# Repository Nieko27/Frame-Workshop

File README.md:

> ⚠️ This is an unofficial 3rd-party project with no association to Valve.

# What is Frame Workshop?
Frame Workshop is intended to be an open-source bundle of different hardware peripherals built around (but not always exclusive to) the Steam Frame. The idea is to leverage the Steam Frames' modularity and general openness to create a collection of open-source hardware projects that the community can provide feedback on, expand upon, or even take and turn into something entirely new, creating a feedback loop that adds to an ever-expanding ecosystem for the Steam Frame. All source files, from schematics to STLs, will be included, allowing every aspect of each project to be modified and produced to anyone’s preferences. 

## Hardware
Below is a list of all currently in development hardware projects, including a brief overview and notes on changes made to the most recent revision.

### Agnostic Facetracker

| 🛑R&D | hw: EV2 | 
| -------- | ------- |

The Frame face tracker is pretty self-explanatory: it is a module that uses a camera for face tracking in social experiences like VRChat. There are 2 versions planned: one built with the steam frame in mind, using its expansion ports, and another that plugs into the back USB port of the frame and uses an ESP32 to run the camera.

>Headset-Agnostic Version EV2

<br>

Link to the agnostic facetracker files:
[Here](https://github.com/Nieko27/Frame-Workshop/tree/main/KICAD%20Projects/FaceTrackers/Primis_FaceTracker)

### Frame Facetracker

| 🛑R&D | hw: EV1 | 
| -------- | ------- |

Link to frame facetracker files:
[Here](https://github.com/Nieko27/Frame-Workshop/tree/main/KICAD%20Projects/FaceTrackers/Frame_FaceTracker)

### Versipellis (General Purpose Dongle)

| 🟠WIP | hw: EV2 | 
| -------- | ------- |

Versipellis is a dongle utilising an nRF52833 intended as a general-purpose dongle for communicating with any Frame-based hardware, whether it be controllers or trackers. It will be programmable by the end user for whatever they intend to use it for. There will be two versions: one utilising no parts smaller than a 0603 package, making it easy to hand-assemble, and another using much smaller parts that, while smaller, will require assembly by a service like JLCPCB.

>Hand-assemblable EV1

<br>

Link to Versipellis' files:
[Here](https://github.com/Nieko27/Frame-Workshop/tree/main/KICAD%20Projects/Dongles/Primis_Versipellis)

### VeriMini

| 🛑R&D | hw: EV1 | 
| -------- | ------- |

Link to VeriMini files:
[Here](https://github.com/Nieko27/Frame-Workshop/tree/main/KICAD%20Projects/Dongles/Primis_VeriMini)

### Locus (Tracker)

| 🟠WIP | hw: EV2 | 
| -------- | ------- |

Locus is intended to be a tracker like Vive or Tundra, but without reliance on lighthouse base stations. Since the Steam Frame isn’t limited to base station vision, trackers being used with it shouldn’t be either. Similar to Versipellis, Locus will also use an nRF52833 along with an LSM6DSV16X IMU. The idea is that it will track similarly to a slime tracker, but also use the Steam Frame’s optical tracking to address the drift problem of EMF trackers. 

Link to Locus' files:
[Here](https://github.com/Nieko27/FrameWork/tree/main/KICAD%20Projects/Primis_Locus)

## Project Status Indicator

| 🔵STATUS | hw: EV1 | fw: v0.0.0 | sw: v0.0.0 |
| -------- | ------- | ---------- | ---------- |

The above status indicator is listed for each Frame Workshop accessory. It shows overall progress as well as the latest upstreamed hardware, firmware, and/or software versions. Here's what each status means:

**🔴R&D**: This accessory is experimental. The latest hardware revision is either untested, incomplete, or broken. Capabilities are unproven. Form factor and design requirements may change entirely. Intended for use by hardware contributors.

**🟠WIP**: The current hardware revision has been tested and is fully capable of meeting established design requirements. Firmware and/or software are in active development. Future hardware revisions may still follow if oversights or improvements are discovered. Intended for use by software contributors.

**🟡PRE**: This accessory has reached a pre-release stage. Hardware is finalized. Firmware and software meets functional requirements but may still be buggy or unintuitive. Documentation is not yet up to release standards. Considered usable for tinkerers and early adopters.

**🟢REL**: This accessory is considered released and fully functional both in software and hardware. Documentation is available to assist with ordering components, assembly, and usage. Software and firmware QOL updates may still follow but will be distributed through user friendly means.

### Future Projects
* USB Hub
* Index speaker mod kit

## Accessories and CAD
While 3D models for each electronics project are in the 3D models folder, I also plan to make several other CAD files available for accessories that don't require electronics. Things like lens caps, headset stands, battery or IO expansion holders, etc.
<br>
https://github.com/Nieko27/Frame-Workshop/tree/main/3D%20Models/Accessories

## Project Goals

* Keep costs to the users as low as possible. You've already spent over a $1000 on the headset itself, so it would be nice not to have to spend another $1000 customizing it to your liking. How this would be achieved is by everything being open and nothing being sold, for example I’m working on a face tracker that takes advantage of the PCIe port on the Frame, the idea is when its done instead of me having to handle production, shipping and all the joys of selling a project I give the source files out with a tutorial on how to order it yourself from a company like JLCPCB. Now, obviously, this still won't be free to the end user, but it will be much cheaper than if I were to sell it. For example, I have made the first prototype of the face-tracker, and in small quantities (5 to be exact), it cost me $25 per board. Compare that to something like the old Vive face trackers, which I think were closer to $100, and you save a nice bit of money. 

* Give the end user total control over the hardware. Don't like how I've done something? Fire up Blender or KiCad and change it yourself to fit whatever need you have in mind. I know not everyone will be able to do this, as it requires familiarity with the software, but it gives people the ability to do so. Obviously, with this in mind, I want to make the experience for everyone as smooth as possible out of the box, so I will be listening to feedback as much as possible to achieve that. 

* Create a feedback loop. I have all this under a CERN-OHL-S-2.0 license, which (as far as I understand) means you can do anything you want with anything in the repo, including selling it for profit, but you must open-source anything you do under the same license. This way it keeps everything open to the community, and every addition helps grow the ecosystem around the Steam Frame. 

## Note
A forewarning, I am very new to electronics design in general. I apologize in advance for any really baffling design decisions. I hope to learn from these projects and will keep them updated as I learn more. Thank you for your patience.

## Ideas
A few ideas for possible mods for the Frame have already been thrown around. If you have an idea for a mod, whether it's a full module or as simple as a 3D-printable counterweight, feel free to open a pull request under the enhancement tag. You may also feel free to email me at nieko972@gmail.com.

### Find me on
* Twitter; https://x.com/Merlinr271
* Bluesky; https://bsky.app/profile/merlin271.bsky.social

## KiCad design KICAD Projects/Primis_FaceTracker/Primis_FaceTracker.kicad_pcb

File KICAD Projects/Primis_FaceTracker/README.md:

### Status

| 🛑R&D | hw: EV2 | 
| -------- | ------- |

> This accessory is experimental. The latest hardware revision is either untested, incomplete, or broken. Capabilities are unproven. Form factor and design requirements may change entirely. Intended for use by hardware contributors.

### TODO
* Copper pads under power supply
* Clean up and condense
* ESD Protection
# Face Tracker (Headset-Agnostic Version)
Headset-agnostic face tracker. Can be used with Frame by using the USB-C port on the battery.
## Current Isseus
Q1 is setup improperly, removing it and R10 as well as bridging the now empty pads solves the issue. Will fix in EV3 along with some changes to layout and LEDs.

### Schematics

### PCB

### EV2

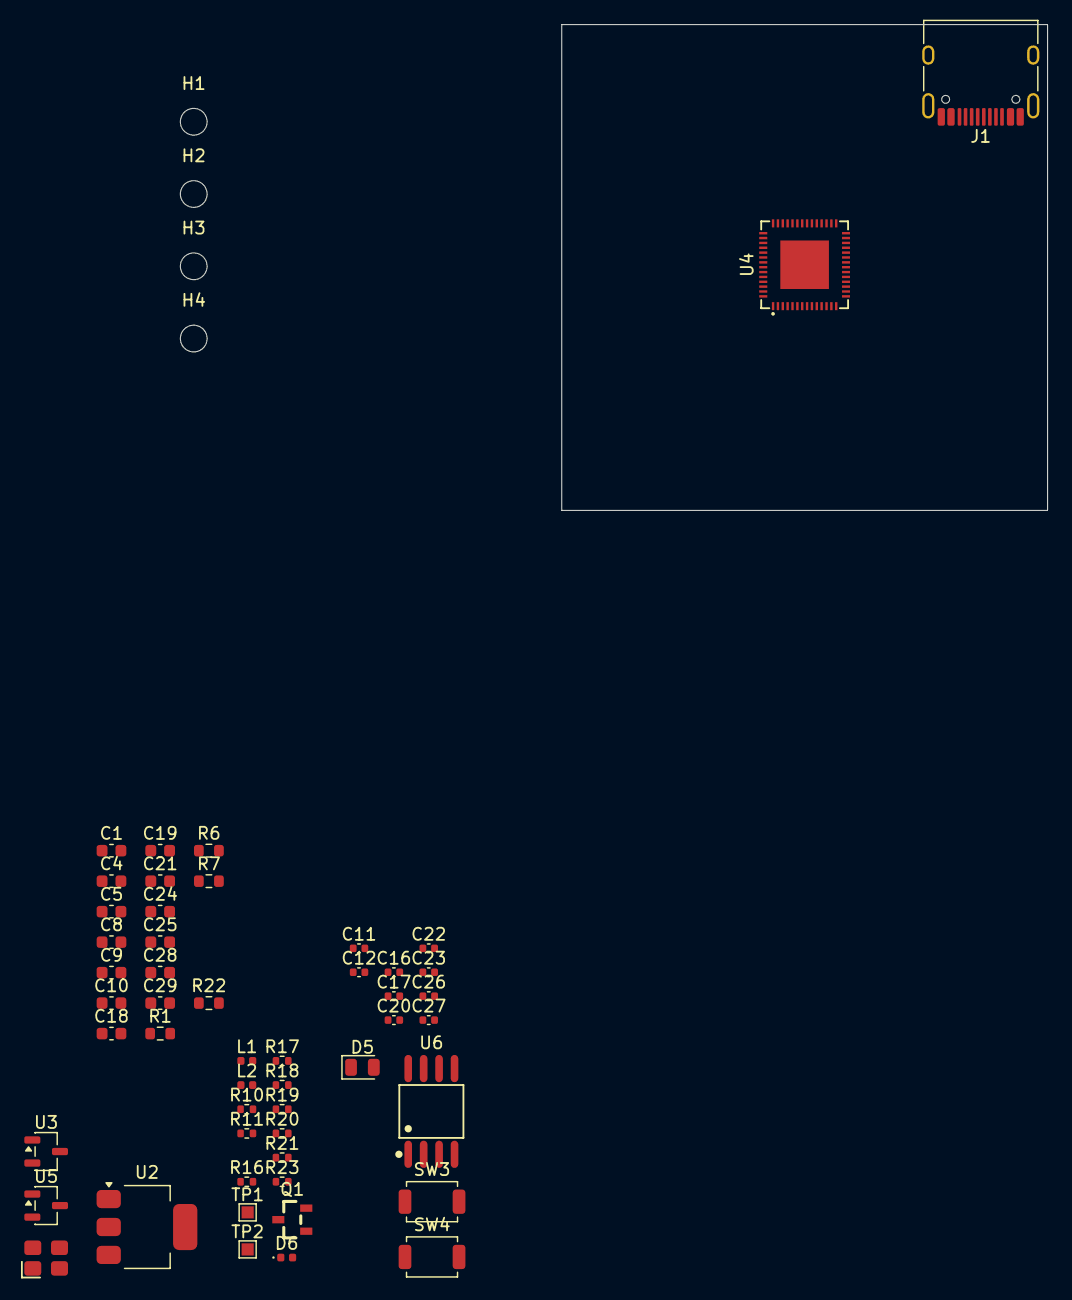
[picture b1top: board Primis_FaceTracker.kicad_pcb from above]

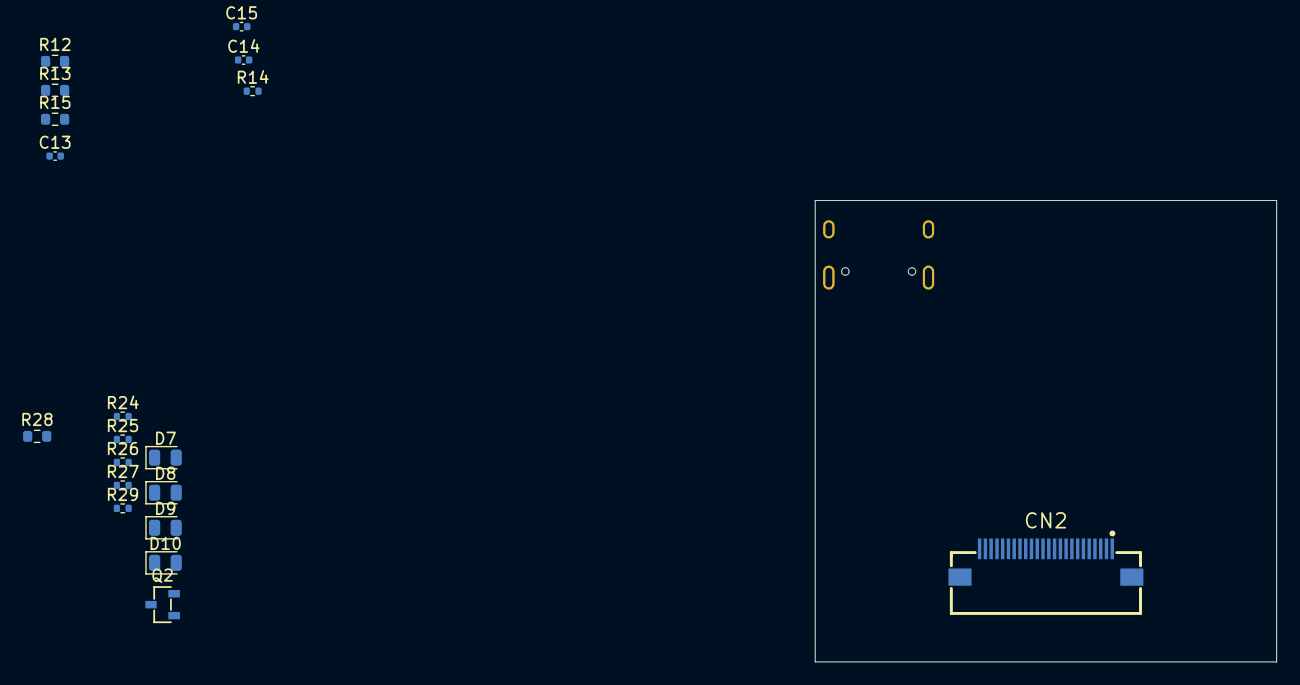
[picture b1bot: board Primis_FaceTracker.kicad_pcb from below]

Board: 2 copper layers, 74 parts (19 on the bottom side), 58 nets, no tracks yet.

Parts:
C1, C4, C8, C9, C10, C19, C24, C28: 10uf; C_0603_1608Metric
C5: 100uf; C_0603_1608Metric
C11, C12, C13, C14, C16, C17, C20, C22, C23: 0.1uf; C_0402_1005Metric
C15: 15pF; C_0402_1005Metric
C18, C21, C25, C29: 1uf; C_0603_1608Metric
C26, C27: 22pf; C_0402_1005Metric
CN2: KH-FG0.5-H2.0-24PIN; FPC-SMD_KH-FG0.5-H2.0-24PIN
D5, D7, D8, D9, D10: LED; LED_0805_2012Metric
D6: D_TVS; D_0402_1005Metric
H1, H2, H3, H4: MountingHole; MountingHole_2.2mm_M2
J1: USB_C_Receptacle_USB2.0_16P; USB_C_Receptacle_HRO_TYPE-C-31-M-12
L1: 2.0nh; L_0402_1005Metric
L2: 24nh; L_0402_1005Metric
Q1: AO3401A
Q2: AO3400A
R1, R22: 10k; R_0603_1608Metric
R6, R7: 5.1k; R_0603_1608Metric
R10, R11, R14: 1k; R_0402_1005Metric
R12, R13, R15: 4.7k; R_0603_1608Metric
R16, R17, R18, R19, R20: 0r; R_0402_1005Metric
R21: 499r; R_0402_1005Metric
R23, R24, R25, R26, R27, R29: 100r; R_0402_1005Metric
R28: 100K; R_0603_1608Metric
SW3, SW4: SW_SPST; SW_SPST_TS-1088-xR020
TP1, TP2: TestPoint; TestPoint_Pad_1.0x1.0mm
U2: AMS1117-3.3; SOT-223-3_TabPin2
U3: XC6206P122MR; SOT-23-3
U4: ESP32-S3_R8
U5: XC6206P282MR; SOT-23-3
U6: W25Q128JVSIQTR
X1: 40MHz, 15pF; OSC-SMD_4P-L3.2-W2.5-BL_SIT8008BI

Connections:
+3V3: C1.1, C5.1, C14.1, C17.1, C18.1, C19.1, C20.1, C23.1, C24.1, C25.1, C28.1, CN2.11, D6.1 (A1), L1.1, Q1.2 (S), R1.2, R11.2, R12.1, R13.1, R15.1, R22.2, R24.2, R25.2, R26.2, R29.2, U2.2 (VO), U4.20 (VDD3P3_RTC), U4.46 (VDD3P3_CPU), U4.55 (VDDA), U4.56 (VDDA)
+5V: C4.1, J1.A4 (VBUS), J1.A9 (VBUS), J1.B4 (VBUS), J1.B9 (VBUS), U2.3 (VI)
BOOT: R23.1, U4.5 (GPIO0)
CAM_1.2V: C10.1, C12.1, CN2.10, U3.2 (VO)
CAM_2.8V: C9.1, C11.1, CN2.4, U5.2 (VO)
CAM_D0: CN2.19, U4.18 (GPIO13)
CAM_D1: CN2.21, U4.23 (GPIO17)
CAM_D2: CN2.22, U4.24 (GPIO18)
CAM_D3: CN2.20, U4.19 (GPIO14)
CAM_D4: CN2.18, U4.17 (GPIO12)
CAM_D5: CN2.16, U4.15 (GPIO10)
CAM_D6: CN2.14, U4.14 (GPIO9)
CAM_D7: CN2.12, U4.12 (GPIO7)
CAM_HSYNC: CN2.9, U4.7 (GPIO2)
CAM_MCLK: CN2.13, U4.13 (GPIO8)
CAM_PCLK: C15.1, CN2.17, U4.16 (GPIO11)
CAM_PWR: R10.1, U4.27 (GPIO21)
CAM_RST: C13.1, CN2.6, R15.2, U4.11 (GPIO6)
CAM_SCK: CN2.5, R12.2, U4.10 (GPIO5)
CAM_SDA: CN2.3, R13.2, U4.9 (GPIO4)
CAM_VSYNC: CN2.7, U4.6 (GPIO1)
D+: J1.A6 (D+), J1.B6 (D+), U4.26 (GPIO20)
D-: J1.A7 (D-), J1.B7 (D-), U4.25 (GPIO19)
EN: C29.1, R22.1, SW3.1 (A), U4.4 (CHIP_PU)
GND: C1.2, C4.2, C5.2, C8.2, C9.2, C10.2, C11.2, C12.2, C13.2, C14.2, C15.2, C16.2, C17.2, C18.2, C19.2, C20.2, C21.2, C22.2, C23.2, C24.2, C25.2, C26.2, C27.2, C28.2, C29.2, CN2.2, CN2.15, CN2.25, CN2.26, D5.1 (K), D6.2 (A2), J1.A1 (GND), J1.A12 (GND), J1.B1 (GND), J1.B12 (GND), Q2.2 (S), R6.1, R7.1, R14.2, R28.1, SW3.2 (B), SW4.2 (B), U2.1 (GND), U3.1 (GND), U4.57 (GND), U5.1 (GND), U6.4 (GND), X1.2 (GND), X1.4 (GND)
LED_PWM: R27.1, U4.43 (GPIO38)
unnamed: C16.1, L1.2, U4.2 (VDD3P3), U4.3 (VDD3P3)
unnamed: C27.1, L2.2, X1.1 (OSC)
unnamed: CN2.8, R14.1
unnamed: D5.2 (A), R11.1
unnamed: D7.2 (A), R24.1
unnamed: D8.2 (A), R25.1
unnamed: D9.2 (A), R26.1
unnamed: D10.2 (A), R29.1
unnamed: D7.1 (K), D8.1 (K), D9.1 (K), D10.1 (K), Q2.3 (D)
unnamed: J1.A5 (CC1), R6.2
unnamed: J1.B5 (CC2), R7.2
unnamed: C8.1, Q1.3 (D), U3.3 (VI), U5.3 (VI)
unnamed: Q1.1 (G), R1.1, R10.2
unnamed: Q2.1 (G), R27.2, R28.2
unnamed: R21.2, TP1.1 (1_1)
unnamed: R23.2, SW4.1 (A)
unnamed: R18.1, U4.33 (SPICLK)
unnamed: R20.1, U4.35 (SPID)
unnamed: R16.1, U4.30 (SPIHD)
unnamed: R19.1, U4.34 (SPIQ)
unnamed: R17.1, U4.31 (SPIWP)
unnamed: TP2.1 (1_1), U4.50 (U0RXD)
unnamed: R21.1, U4.49 (U0TXD)
unnamed: C26.1, U4.53 (XTAL_N), X1.3 (OSC)
unnamed: L2.1, U4.54 (XTAL_P)
SPICLK: R18.2, U6.6 (CLK)
SPICS0: U4.32 (SPICS0), U6.1 (CS#)
SPID: R20.2, U6.5 (DI)
SPIHD: R16.2, U6.7 (IO3)
SPIQ: R19.2, U6.2 (DO)
SPIWP: R17.2, U6.3 (IO2)
VDD_SPI: C21.1, C22.1, U4.29 (VDD_SPI), U6.8 (VCC)

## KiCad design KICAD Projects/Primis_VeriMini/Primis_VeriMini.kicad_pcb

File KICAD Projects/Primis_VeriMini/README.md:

### Status

| 🛑R&D | hw: EV1 | 
| -------- | ------- |

> This accessory is experimental. The latest hardware revision is either untested, incomplete, or broken. Capabilities are unproven. Form factor and design requirements may change entirely. Intended for use by hardware contributors.

# VERI-MINI
The general purpose dongle for the Steam Frame but smaller.

### Schematics

### PCB

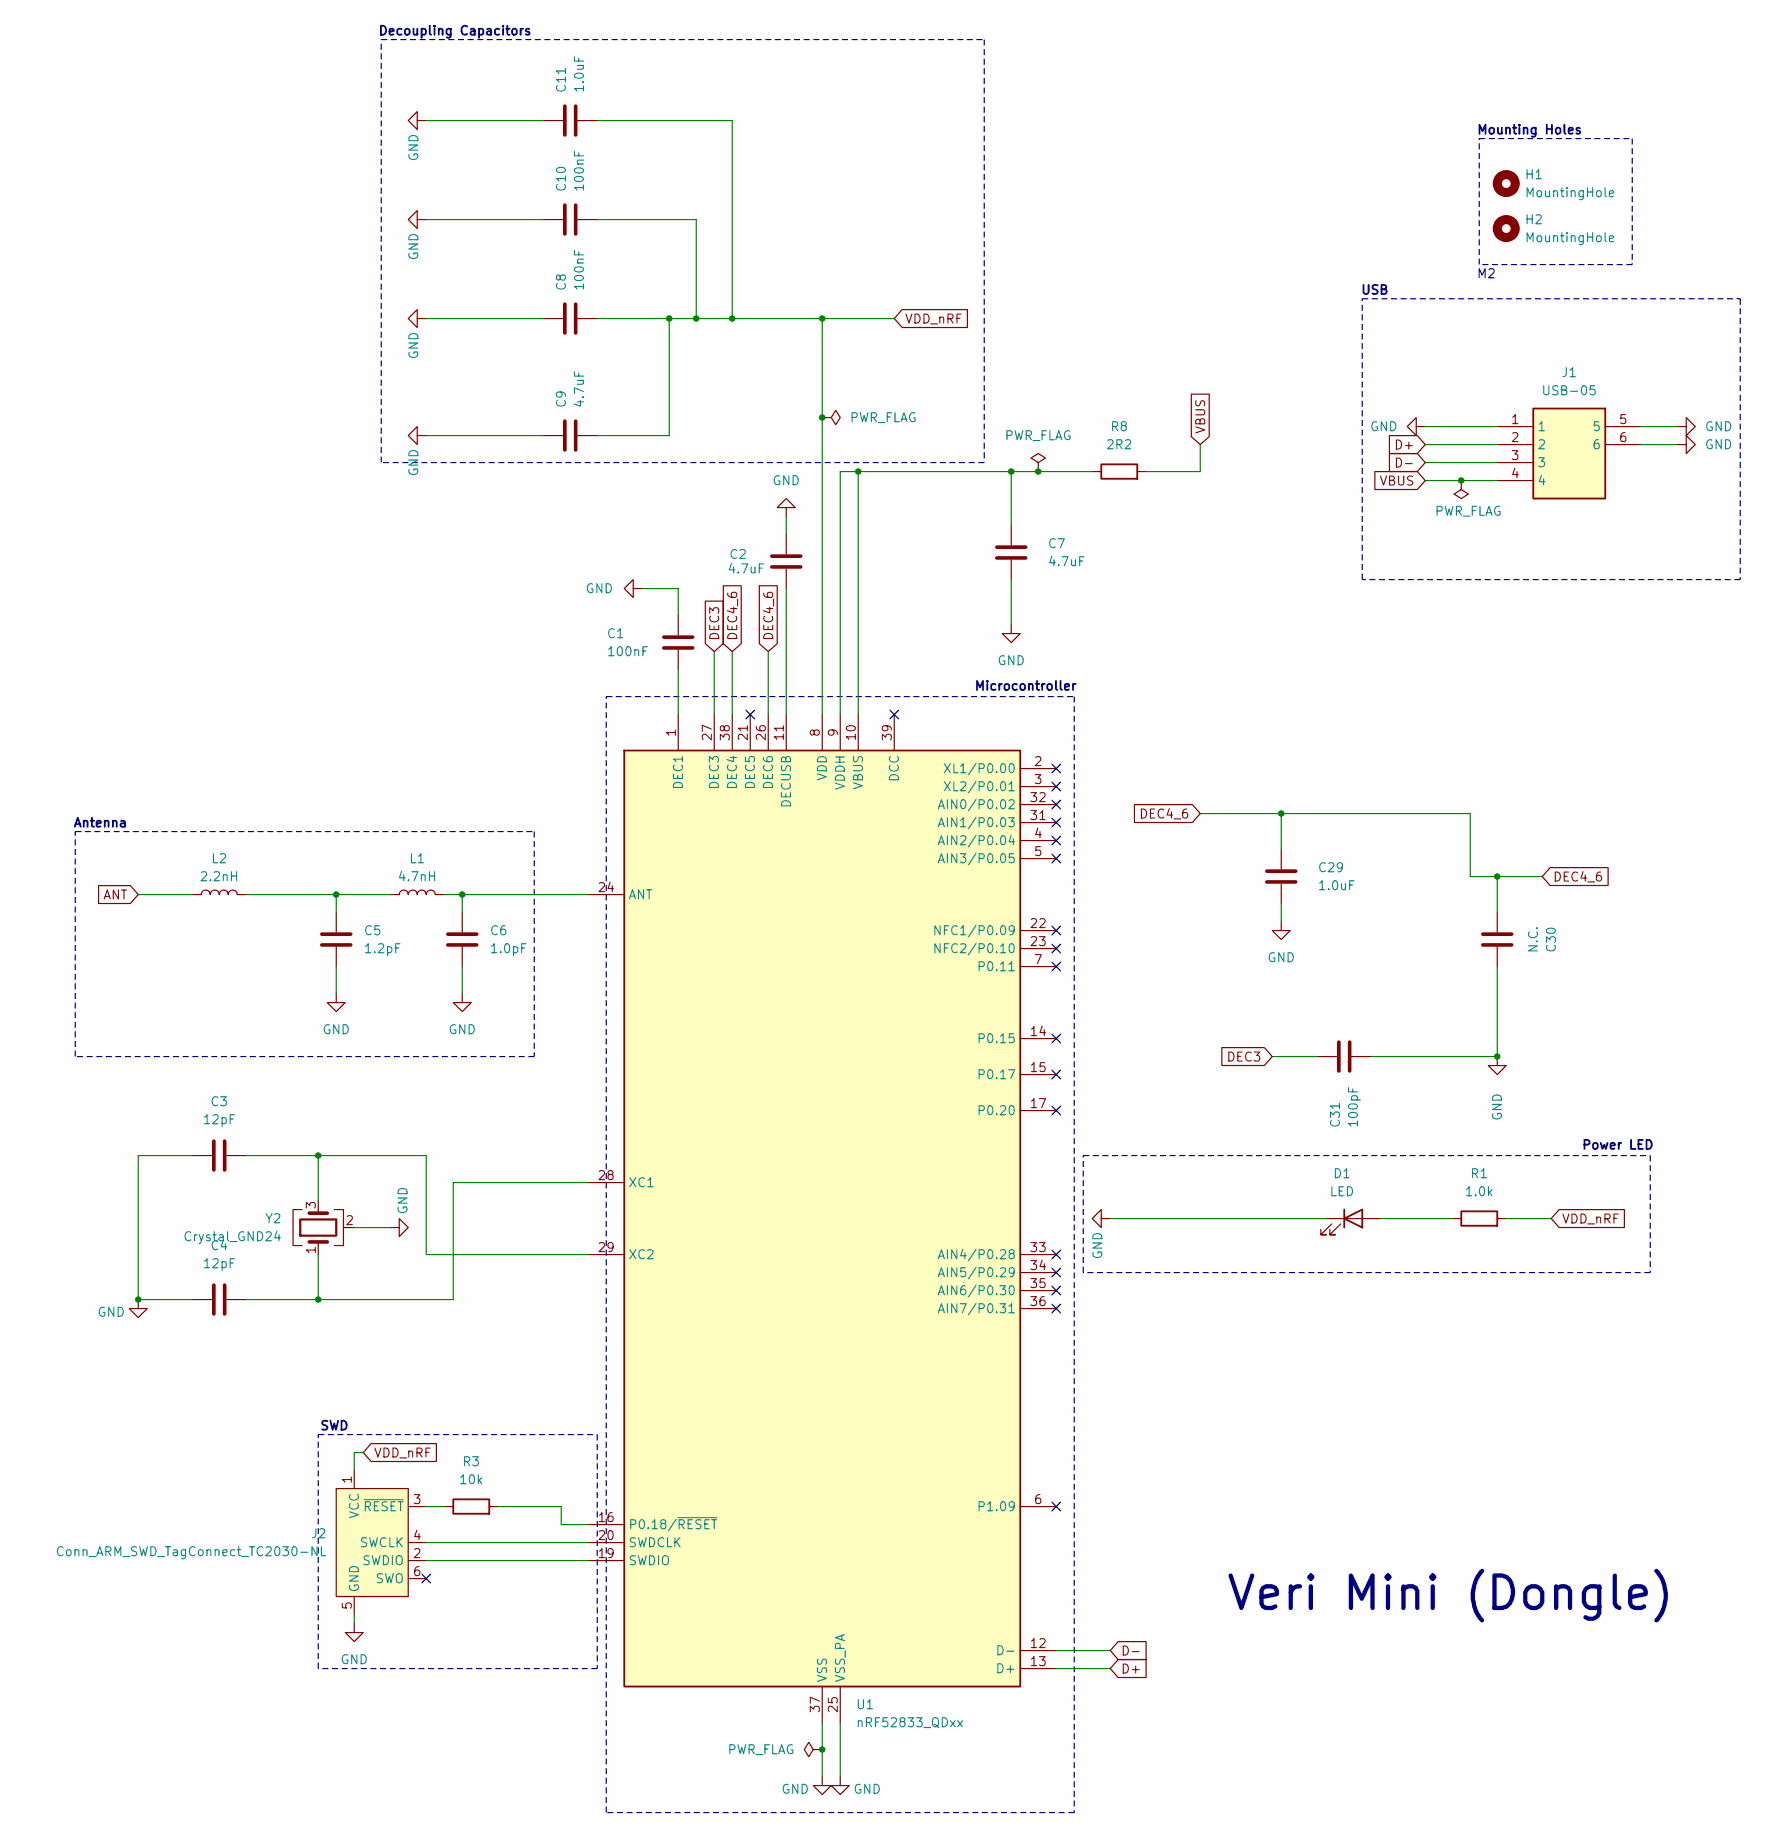
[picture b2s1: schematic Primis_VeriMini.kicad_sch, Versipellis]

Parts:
C1, C8, C10: 100nF; C_0402_1005Metric
C2, C7, C9: 4.7uF; C_0603_1608Metric
C3, C4: 12pF; C_0402_1005Metric
C5: 1.2pF; C_0402_1005Metric
C6: 1.0pF; C_0402_1005Metric
C11, C29: 1.0uF; C_0402_1005Metric
C30: N.C.; C_0402_1005Metric
C31: 100pF; C_0402_1005Metric
D1: LED; LED_0603_1608Metric
H1, H2: MountingHole; MountingHole_2.2mm_M2
J1: USB-05; USB05; Manufacturer_Part_Number USB-05
J2: Conn_ARM_SWD_TagConnect_TC2030-NL; Tag-Connect_TC2030-IDC-NL_2x03_P1.27mm_Vertical
L1: 4.7nH; L_0402_1005Metric
L2: 2.2nH; L_0402_1005Metric
R1: 1.0k; R_0402_1005Metric
R3: 10k; R_0603_1608Metric
R8: 2R2; R_0603_1608Metric
U1: nRF52833_QDxx; QFN-40-1EP_5x5mm_P0.4mm_EP3.6x3.6mm
Y2: Crystal_GND24; Crystal_SMD_Abracon_ABM8G-4Pin_3.2x2.5mm

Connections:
ANT: L2.1
D+: J1.2, U1.13 (D+)
D-: J1.3, U1.12 (D-)
DEC3: C31.1, U1.27 (DEC3)
DEC4_6: C29.1, C30.2, U1.26 (DEC6), U1.38 (DEC4)
GND: C1.1, C2.2, C3.1, C4.1, C5.1, C6.1, C7.2, C8.1, C9.2, C10.1, C11.2, C29.2, C30.1, C31.2, D1.1 (K), J1.1, J1.5, J1.6, J2.5 (GND), U1.25 (VSS_PA), U1.37 (VSS), U1.41 (VSS), Y2.2 (G), Y2.4 (G)
unnamed: C5.2, L1.1, L2.2
unnamed: D1.2 (A), R1.1
unnamed: J2.4 (SWCLK), U1.20 (SWDCLK)
unnamed: J2.2 (SWDIO), U1.19 (SWDIO)
unnamed: J2.3 (~RESET), R3.1
unnamed: C6.2, L1.2, U1.24 (ANT)
unnamed: C1.2, U1.1 (DEC1)
unnamed: C2.1, U1.11 (DECUSB)
unnamed: R3.2, U1.16 (P0.18/~RESET)
unnamed: C7.1, R8.1, U1.9 (VDDH), U1.10 (VBUS)
unnamed: C4.2, U1.28 (XC1), Y2.1
unnamed: C3.2, U1.29 (XC2), Y2.3
VBUS: J1.4, R8.2
VDD_nRF: C8.2, C9.1, C10.2, C11.1, J2.1 (VCC), R1.2, U1.8 (VDD), U1.18 (VDD), U1.30 (VDD), U1.40 (VDD)

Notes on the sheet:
Mounting Holes
Decoupling Capacitors
Microcontroller
Veri Mini (Dongle)
SWD
Antenna
Power LED
USB

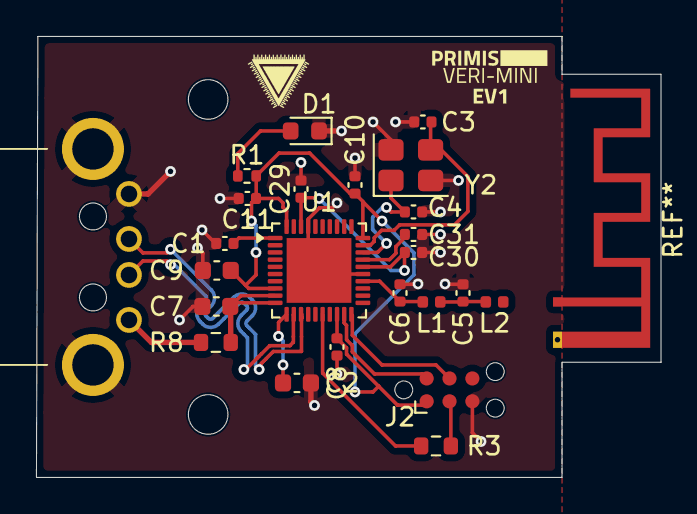
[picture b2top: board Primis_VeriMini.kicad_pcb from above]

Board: 2 copper layers, 34.7 x 24.5 mm, 26 parts (0 on the bottom side), 19 nets.

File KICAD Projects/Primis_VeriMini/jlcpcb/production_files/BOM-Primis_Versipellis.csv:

Comment,Designator,Footprint,LCSC,Quantity
1.2pF,C5,C_0603_1608Metric,,1
2R2,R8,R_0805_2012Metric,,1
1.0pF,C6,C_0603_1608Metric,,1
12pF,C4,C_0603_1608Metric,,1
4.7uF,C2,C_0603_1608Metric,,1
USB-05,J1,USB05,,1
WS2812B-2020,D3,LED_WS2812B-2020_PLCC4_2.0x2.0mm,,1
4.7uF,C9,C_0603_1608Metric,,1
nRF52833_QDxx,U1,QFN-40-1EP_5x5mm_P0.4mm_EP3.6x3.6mm,,1
100nF,C8,C_0603_1608Metric,,1
12pF,C3,C_0603_1608Metric,,1
100pF,C31,C_0603_1608Metric,,1
1.0k,R1,R_0603_1608Metric,,1
4.7uF,C7,C_0603_1608Metric,,1
LED,D1,LED_0603_1608Metric,,1
N.C.,C30,C_0603_1608Metric,,1
1.0uF,C29,C_0603_1608Metric,,1
1.0uF,C11,C_0603_1608Metric,,1
Crystal_GND24,Y2,Crystal_SMD_Abracon_ABM8G-4Pin_3.2x2.5mm,,1
100nF,C10,C_0603_1608Metric,,1
2.2nH,L2,L_0603_1608Metric,,1
10k,R3,R_0603_1608Metric,,1
4.7nH,L1,L_0603_1608Metric,,1
100nF,C1,C_0603_1608Metric,,1
100nF,C12,C_0603_1608Metric,,1

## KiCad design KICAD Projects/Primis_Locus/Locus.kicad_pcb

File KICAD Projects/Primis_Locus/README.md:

### Status

| 🟠WIP | hw: EV2 | 
| -------- | ------- |

> The current hardware revision has been tested and is fully capable of meeting established design requirements. Firmware and/or software are in active development. Future hardware revisions may still follow if oversights or improvements are discovered. Intended for use by software contributors.

### Schematics

### PCB

### EV1

### EV2

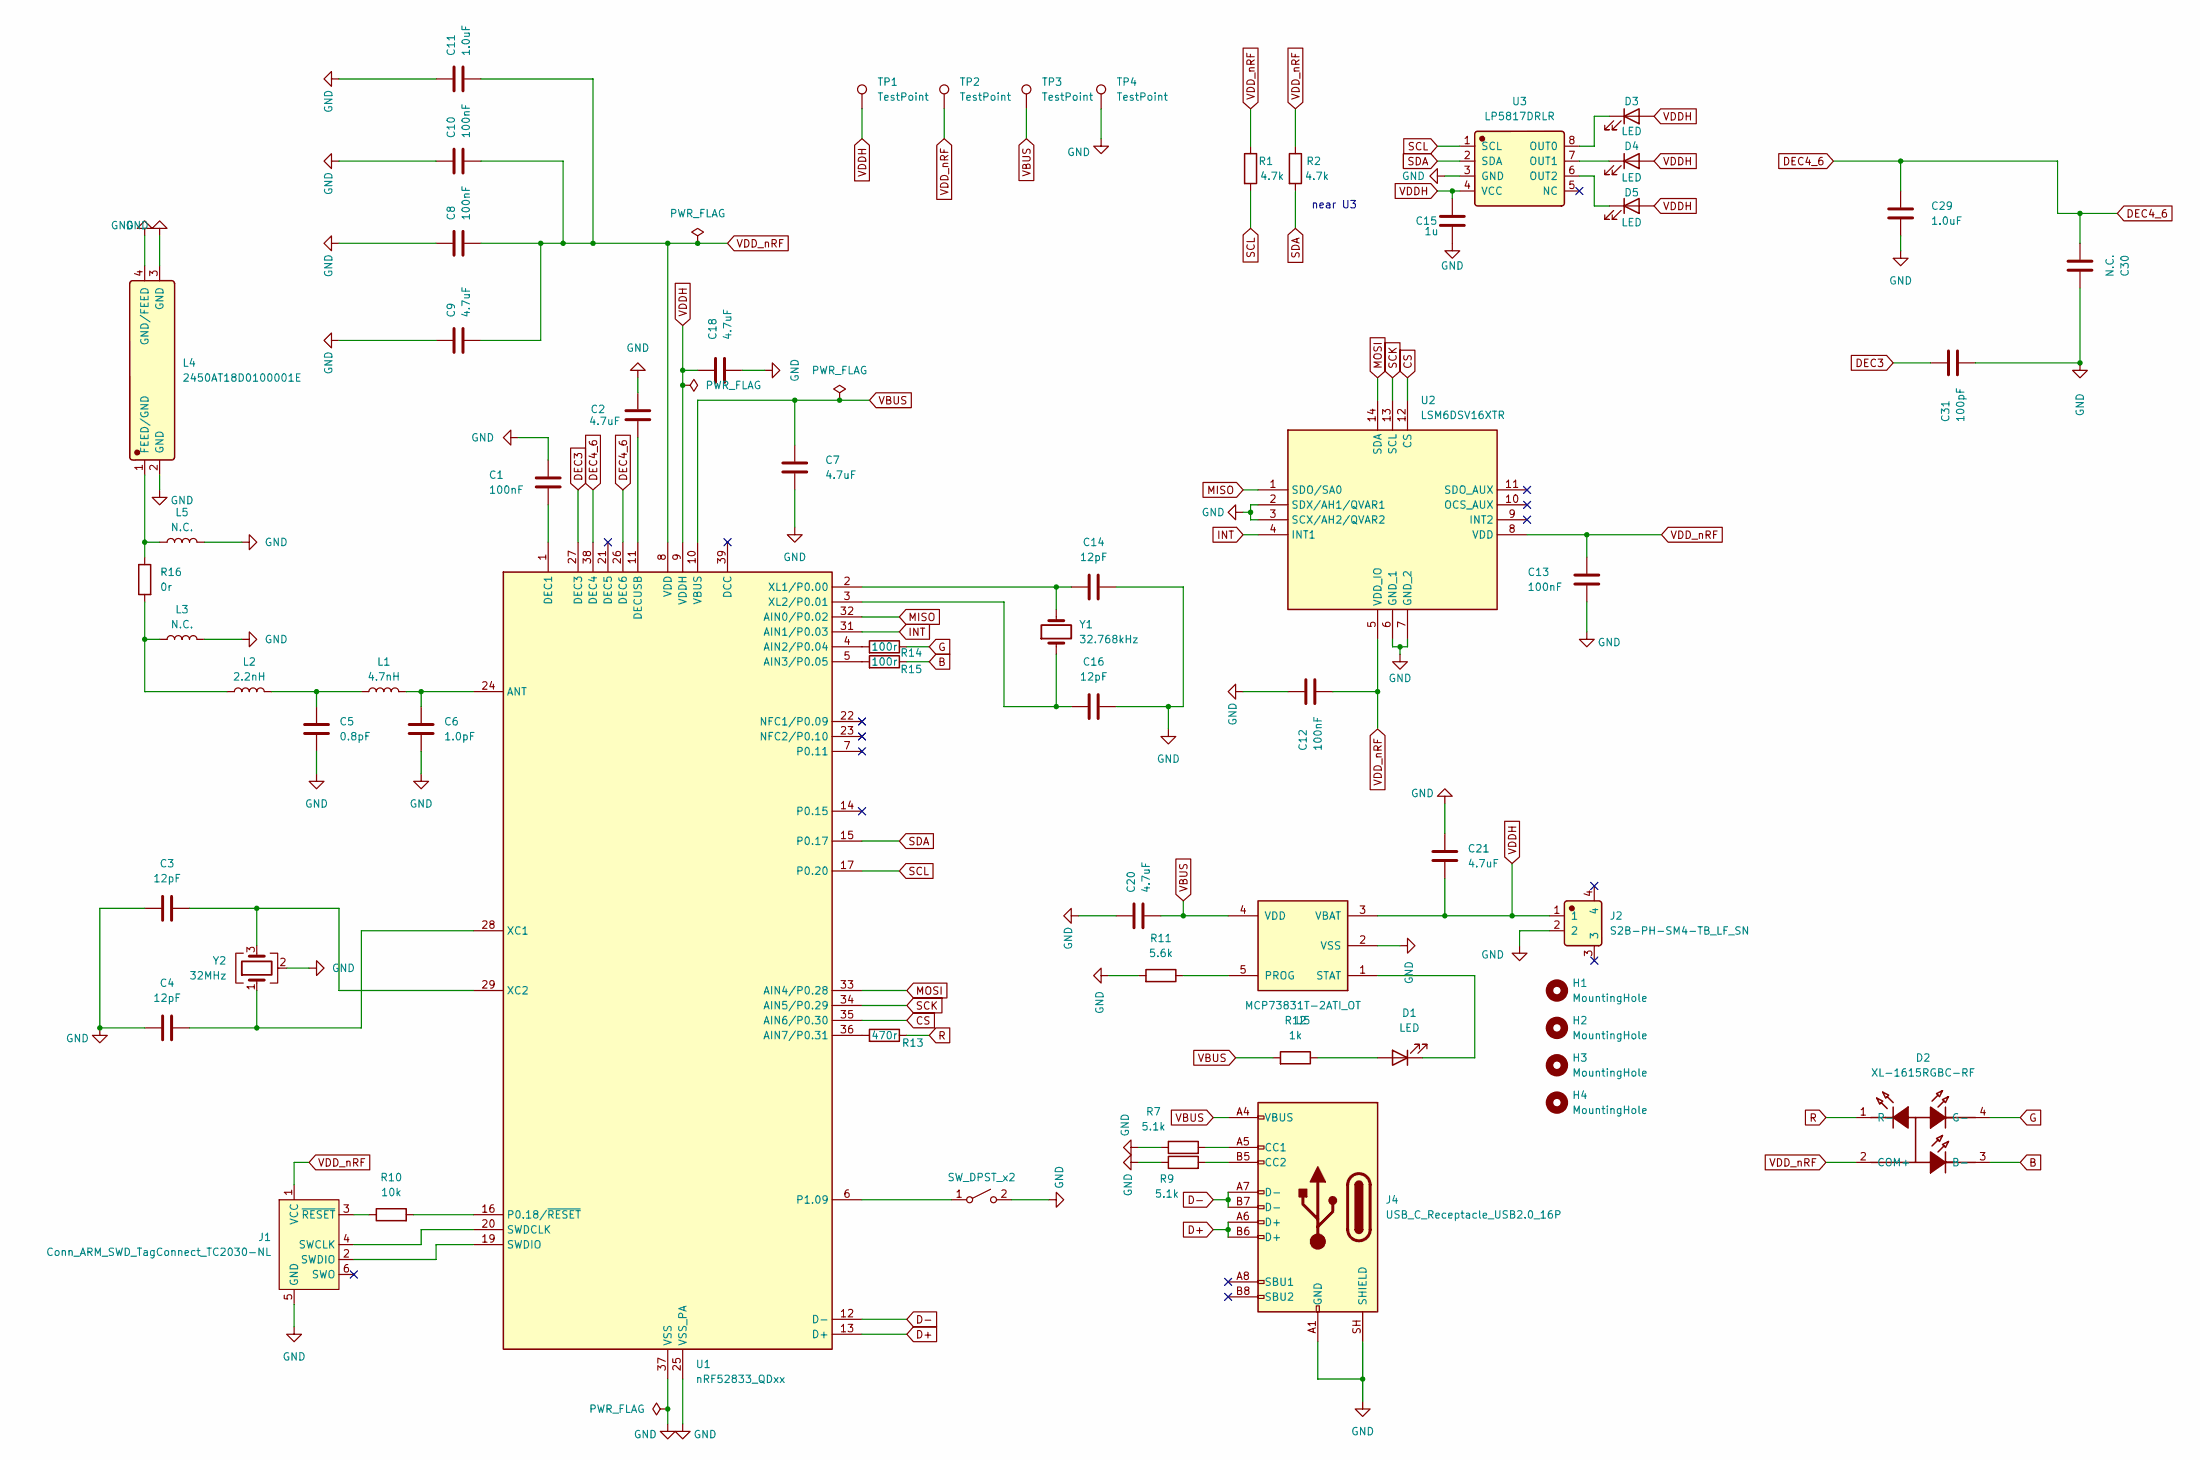
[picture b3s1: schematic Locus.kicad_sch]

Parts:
C1, C8, C10, C12, C13: 100nF; C_0402_1005Metric
C2, C7, C9, C18, C20, C21: 4.7uF; C_0603_1608Metric
C3, C4, C14, C16: 12pF; C_0402_1005Metric
C5: 0.8pF; C_0402_1005Metric
C6: 1.0pF; C_0402_1005Metric
C11, C29: 1.0uF; C_0402_1005Metric
C15: 1u; C_0402_1005Metric
C30: N.C.; C_0402_1005Metric
C31: 100pF; C_0402_1005Metric
D1: LED; LED_0603_1608Metric
D2: XL-1615RGBC-RF; Manufacturer Part XL-1615RGBC-RF; LCSC C965840
D3, D4, D5: LED; LED_0805_2012Metric
H1, H2, H3, H4: MountingHole; MountingHole_2.7mm_M2.5
J1: Conn_ARM_SWD_TagConnect_TC2030-NL; Tag-Connect_TC2030-IDC-NL_2x03_P1.27mm_Vertical
J2: S2B-PH-SM4-TB_LF_SN; Manufacturer Part S2B-PH-SM4-TB(LF)(SN); LCSC C295747
J4: USB_C_Receptacle_USB2.0_16P; USB_C_Receptacle_HRO_TYPE-C-31-M-12
L1: 4.7nH; L_0402_1005Metric
L2: 2.2nH; L_0402_1005Metric
L3, L5: N.C.; L_0402_1005Metric
L4: 2450AT18D0100001E; Manufacturer Part 2450AT18D0100001E; LCSC C7450310
R1, R2: 4.7k; R_0402_1005Metric
R7, R9: 5.1k; R_0402_1005Metric
R10: 10k; R_0402_1005Metric
R11: 5.6k; R_0402_1005Metric
R12: 1k; R_0402_1005Metric
R13: 470r; R_0402_1005Metric
R14, R15: 100r; R_0402_1005Metric
R16: 0r; R_0402_1005Metric
SW1: SW_DPST_x2; SH-1806SA-A3DW-04
TP1, TP2, TP3, TP4: TestPoint; TestPoint_Pad_1.0x1.0mm
U1: nRF52833_QDxx; QFN-40-1EP_5x5mm_P0.4mm_EP3.6x3.6mm
U2: LSM6DSV16XTR; LSM6DSV16BXTR; Manufacturer_Part_Number LSM6DSV16XTR; Mouser Part Number 511-LSM6DSV16XTR
U3: LP5817DRLR; Manufacturer Part LP5817DRLR; LCSC C47262829
U5: MCP73831T-2ATI_OT; Manufacturer Part MCP73831T-2ATI/OT; LCSC C14879
Y1: 32.768kHz; SC-20S32_768kHz20PPM9pF
Y2: 32MHz; NX2016SA-32MHZ-STD-CZS-5

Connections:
B: D2.3 (B-), R15.1
CS: U1.35 (AIN6/P0.30), U2.12 (CS)
D+: J4.A6 (D+), J4.B6 (D+), U1.13 (D+)
D-: J4.A7 (D-), J4.B7 (D-), U1.12 (D-)
DEC3: C31.1, U1.27 (DEC3)
DEC4_6: C29.1, C30.2, U1.26 (DEC6), U1.38 (DEC4)
G: D2.4 (G-), R14.1
GND: C1.1, C2.2, C3.1, C4.1, C5.1, C6.1, C7.2, C8.1, C9.2, C10.1, C11.2, C12.1, C13.2, C14.1, C15.2, C16.2, C18.2, C20.2, C21.1, C29.2, C30.1, C31.2, J1.5 (GND), J2.2, J4.A1 (GND), J4.A12 (GND), J4.B1 (GND), J4.B12 (GND), J4.SH (SHIELD), L3.2, L4.2 (GND), L4.3 (GND), L4.4 (GND/FEED), L5.2, R7.1, R9.1, R11.2, SW1.2 (B), TP4.1 (1_1), U1.25 (VSS_PA), U1.37 (VSS), U1.41 (VSS), U2.2 (SDX/AH1/QVAR1), U2.3 (SCX/AH2/QVAR2), U2.6 (GND_1), U2.7 (GND_2), U3.3 (GND), U5.2 (VSS), Y2.2 (G), Y2.4 (G)
INT: U1.31 (AIN1/P0.03), U2.4 (INT1)
MISO: U1.32 (AIN0/P0.02), U2.1 (SDO/SA0)
MOSI: U1.33 (AIN4/P0.28), U2.14 (SDA)
unnamed: C5.2, L1.1, L2.2
unnamed: D1.2 (A), R12.1
unnamed: D1.1 (K), U5.1 (STAT)
unnamed: D3.1 (K), U3.8 (OUT0)
unnamed: D4.1 (K), U3.7 (OUT1)
unnamed: D5.1 (K), U3.6 (OUT2)
unnamed: J1.4 (SWCLK), U1.20 (SWDCLK)
unnamed: J1.2 (SWDIO), U1.19 (SWDIO)
unnamed: J1.3 (~RESET), R10.1
unnamed: J4.A5 (CC1), R7.2
unnamed: J4.B5 (CC2), R9.2
unnamed: L2.1, L3.1, R16.2
unnamed: L4.1 (FEED/GND), L5.1, R16.1
unnamed: SW1.1 (A), U1.6 (P1.09)
unnamed: R14.2, U1.4 (AIN2/P0.04)
unnamed: R15.2, U1.5 (AIN3/P0.05)
unnamed: R13.2, U1.36 (AIN7/P0.31)
unnamed: C6.2, L1.2, U1.24 (ANT)
unnamed: C1.2, U1.1 (DEC1)
unnamed: C2.1, U1.11 (DECUSB)
unnamed: R10.2, U1.16 (P0.18/~RESET)
unnamed: C4.2, U1.28 (XC1), Y2.1
unnamed: C3.2, U1.29 (XC2), Y2.3
unnamed: C14.2, U1.2 (XL1/P0.00), Y1.2
unnamed: C16.1, U1.3 (XL2/P0.01), Y1.1
unnamed: R11.1, U5.5 (PROG)
R: D2.1 (R-), R13.1
SCK: U1.34 (AIN5/P0.29), U2.13 (SCL)
SCL: R1.2, U1.17 (P0.20), U3.1 (SCL)
SDA: R2.2, U1.15 (P0.17), U3.2 (SDA)
VBUS: C7.1, C20.1, J4.A4 (VBUS), J4.A9 (VBUS), J4.B4 (VBUS), J4.B9 (VBUS), R12.2, TP3.1 (1_1), U1.10 (VBUS), U5.4 (VDD)
VDDH: C15.1, C18.1, C21.2, D3.2 (A), D4.2 (A), D5.2 (A), J2.1, TP1.1 (1_1), U1.9 (VDDH), U3.4 (VCC), U5.3 (VBAT)
VDD_nRF: C8.2, C9.1, C10.2, C11.1, C12.2, C13.1, D2.2 (COM+), J1.1 (VCC), R1.1, R2.1, TP2.1 (1_1), U1.8 (VDD), U1.18 (VDD), U1.30 (VDD), U1.40 (VDD), U2.5 (VDD_IO), U2.8 (VDD)

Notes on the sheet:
near U3

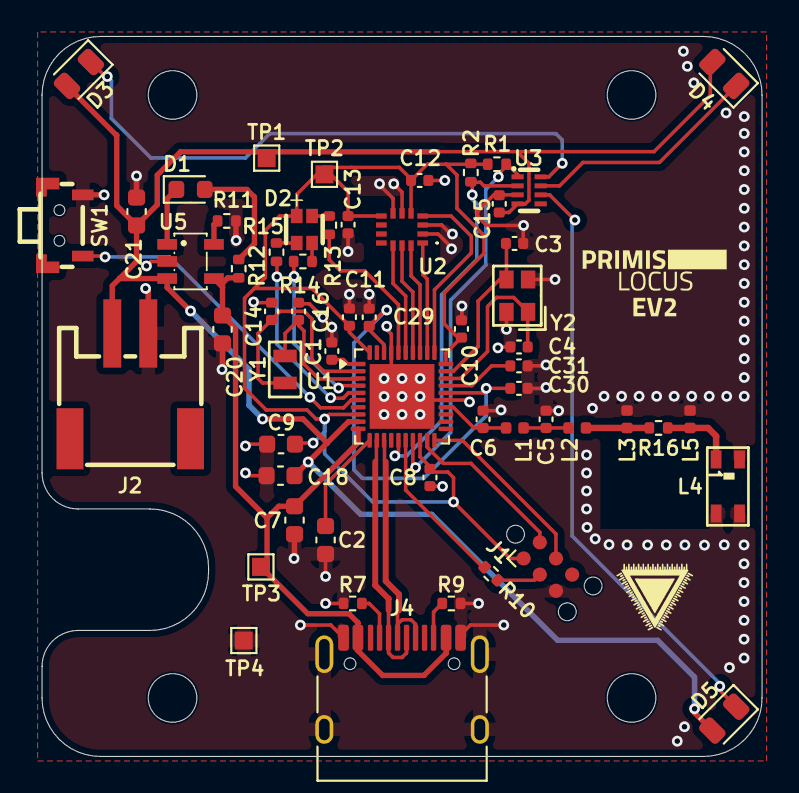
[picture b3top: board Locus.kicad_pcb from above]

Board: 4 copper layers, 40.0 x 40.0 mm, 61 parts (0 on the bottom side), 44 nets.

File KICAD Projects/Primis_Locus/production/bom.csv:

Designator,Footprint,Quantity,Value,LCSC Part #
"C1, C10, C12, C13, C8",0402,5,100nF,
"C11, C29",0402,2,1.0uF,
"C14, C16, C3, C4",0402,4,12pF,
C17,0603,1,2.2uF,
"C18, C2, C20, C21, C7, C9",0603,6,4.7uF,
"C30, L3, L5",0402,3,N.C.,
C31,0402,1,100pF,
C5,0402,1,0.8pF,
C6,0402,1,1.0pF,
D1,0603,1,LED,
D2,XL-1615RGBC-RF,1,XL-1615RGBC-RF,C965840
J2,S2B-PH-SM4-TB_LF_SN,1,S2B-PH-SM4-TB_LF_SN,C295747
J4,USB_C_Receptacle_HRO_TYPE-C-31-M-12,1,USB_C_Receptacle_USB2.0_16P,
L1,0402,1,4.7nH,
L2,0402,1,2.2nH,
L4,2450AT18D0100001E,1,2450AT18D0100001E,C7450310
"R1, R2, R4",0402,3,4.7k,
R10,0402,1,10k,
R11,0402,1,5.6k,
R12,0402,1,1k,
R13,0402,1,470r,
"R14, R15",0402,2,100r,
R16,0402,1,0r,
"R7, R9",0402,2,5.1k,
SW1,SH-1806SA-A3DW-04,1,SW_DPST_x2,C22383476
"TP1, TP2, TP3, TP4",TestPoint_Pad_1.0x1.0mm,4,TestPoint,
U1,QFN-40-1EP_5x5mm_P0.4mm_EP3.6x3.6mm,1,nRF52833_QDxx,
U2,LSM6DSV16BXTR,1,LSM6DSV16XTR,
U3,QMC6309,1,QMC6309,
U5,MCP73831T-2ATI_OT,1,MCP73831T-2ATI_OT,C14879
Y1,SC-20S32_768kHz20PPM9pF,1,32.768kHz,C97603
Y2,NX2016SA-32MHZ-STD-CZS-5,1,32MHz,C843260

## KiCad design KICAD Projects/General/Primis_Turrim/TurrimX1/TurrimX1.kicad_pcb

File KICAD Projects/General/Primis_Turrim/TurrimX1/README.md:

### WARNING
This has yet to be produced by me yet, I have not yet added the gerber files to this repo yet as I have no idea if it will work yet, order them at your own risk.
# Dongle Dock (1-Port)
Headset-agnostic face tracker. Can be used with Frame by using the USB-C port on the battery.

### Schematics

### PCB

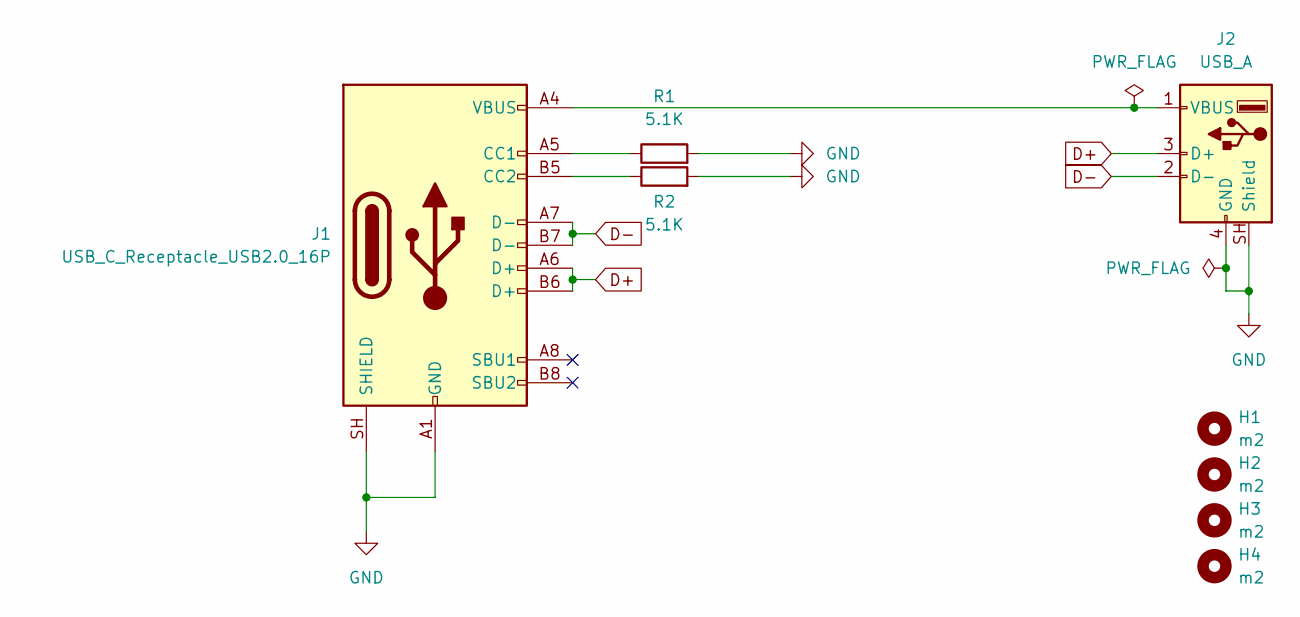
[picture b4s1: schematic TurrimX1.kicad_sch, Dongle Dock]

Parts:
H1, H2, H3, H4: m2; MountingHole_2.2mm_M2
J1: USB_C_Receptacle_USB2.0_16P; USB_C_Receptacle_HRO_TYPE-C-31-M-12
J2: USB_A; USB_A_Molex_105057_Vertical
R1, R2: 5.1K; R_0805_2012Metric

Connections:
D+: J1.A6 (D+), J1.B6 (D+), J2.3 (D+)
D-: J1.A7 (D-), J1.B7 (D-), J2.2 (D-)
GND: J1.A1 (GND), J1.A12 (GND), J1.B1 (GND), J1.B12 (GND), J1.SH (SHIELD), J2.4 (GND), J2.SH (Shield), R1.2, R2.2
unnamed: J1.A5 (CC1), R1.1
unnamed: J1.B5 (CC2), R2.1
unnamed: J1.A4 (VBUS), J1.A9 (VBUS), J1.B4 (VBUS), J1.B9 (VBUS), J2.1 (VBUS)

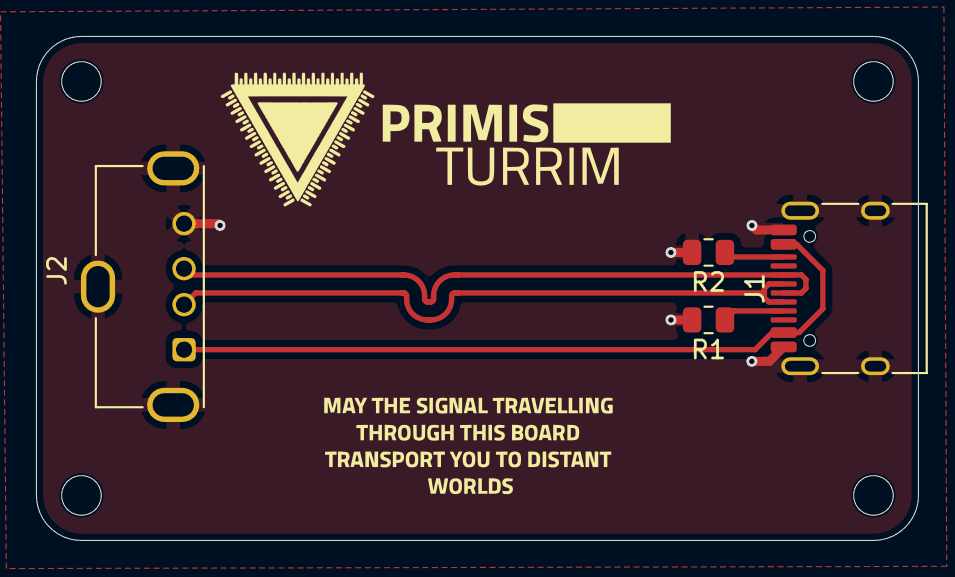
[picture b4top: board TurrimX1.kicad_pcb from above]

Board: 2 copper layers, 49.0 x 28.0 mm, 8 parts (0 on the bottom side), 6 nets.

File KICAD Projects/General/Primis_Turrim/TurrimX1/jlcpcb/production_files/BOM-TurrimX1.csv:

Comment,Designator,Footprint,LCSC,Quantity
5.1K,R2,R_0805_2012Metric,,1
5.1K,R1,R_0805_2012Metric,,1
USB_A,J2,USB_A_Molex_105057_Vertical,,1
USB_C_Receptacle_USB2.0_16P,J1,USB_C_Receptacle_HRO_TYPE-C-31-M-12,,1
